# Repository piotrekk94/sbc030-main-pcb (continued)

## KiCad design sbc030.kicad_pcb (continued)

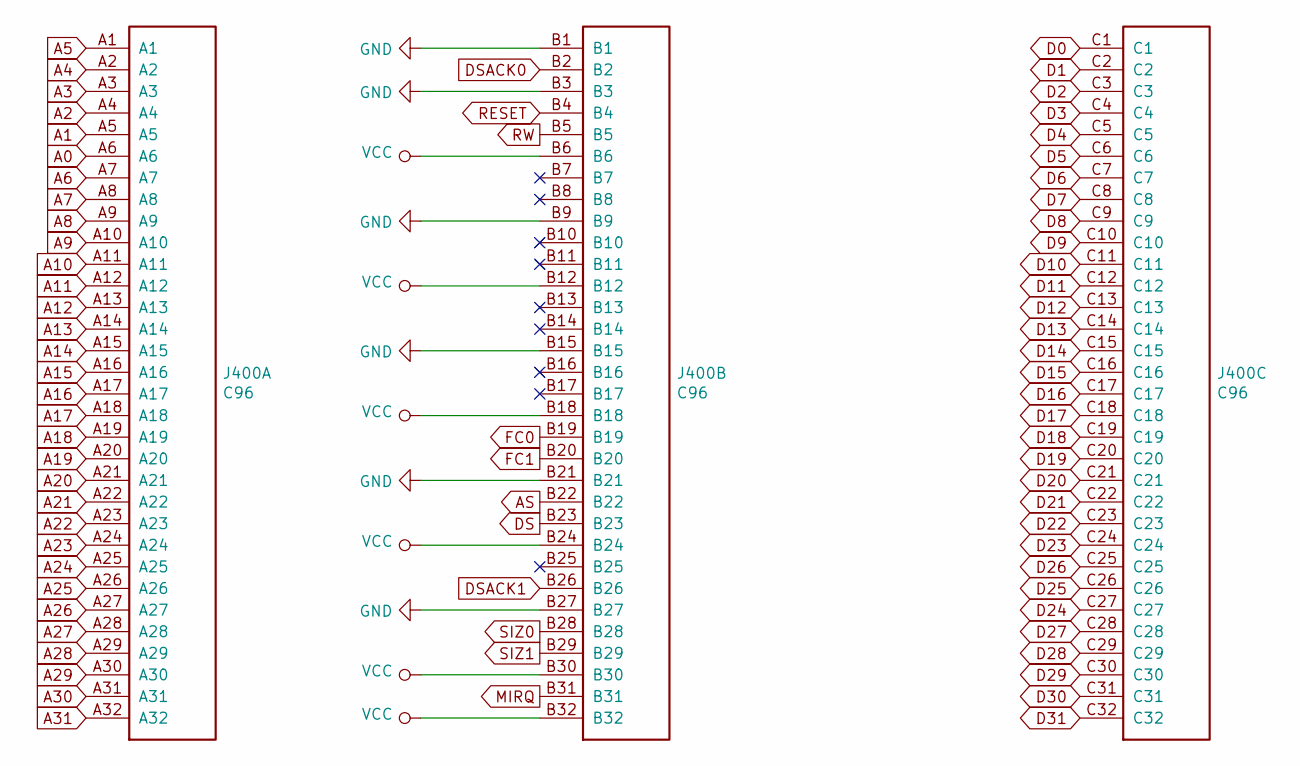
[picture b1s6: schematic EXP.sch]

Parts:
J400: C96; C96ABCM

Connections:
A0: J400.A6; also elsewhere on the board
A1: J400.A5; also elsewhere on the board
A2: J400.A4; also elsewhere on the board
A3: J400.A3; also elsewhere on the board
A4: J400.A2; also elsewhere on the board
A5: J400.A1; also elsewhere on the board
A6: J400.A7; also elsewhere on the board
A7: J400.A8; also elsewhere on the board
A8: J400.A9; also elsewhere on the board
A9: J400.A10; also elsewhere on the board
A10: J400.A11; also elsewhere on the board
A11: J400.A12; also elsewhere on the board
A12: J400.A13; also elsewhere on the board
A13: J400.A14; also elsewhere on the board
A14: J400.A15; also elsewhere on the board
A15: J400.A16; also elsewhere on the board
A16: J400.A17; also elsewhere on the board
A17: J400.A18; also elsewhere on the board
A18: J400.A19; also elsewhere on the board
A19: J400.A20; also elsewhere on the board
A20: J400.A21; also elsewhere on the board
A21: J400.A22; also elsewhere on the board
A22: J400.A23; also elsewhere on the board
A23: J400.A24; also elsewhere on the board
A24: J400.A25; also elsewhere on the board
A25: J400.A26; also elsewhere on the board
A26: J400.A27; also elsewhere on the board
A27: J400.A28; also elsewhere on the board
A28: J400.A29; also elsewhere on the board
A29: J400.A30; also elsewhere on the board
A30: J400.A31; also elsewhere on the board
A31: J400.A32; also elsewhere on the board
AS: J400.B22; also elsewhere on the board
D0: J400.C1; also elsewhere on the board
D1: J400.C2; also elsewhere on the board
D2: J400.C3; also elsewhere on the board
D3: J400.C4; also elsewhere on the board
D4: J400.C5; also elsewhere on the board
D5: J400.C6; also elsewhere on the board
D6: J400.C7; also elsewhere on the board
D7: J400.C8; also elsewhere on the board
D8: J400.C9; also elsewhere on the board
D9: J400.C10; also elsewhere on the board
D10: J400.C11; also elsewhere on the board
D11: J400.C12; also elsewhere on the board
D12: J400.C13; also elsewhere on the board
D13: J400.C14; also elsewhere on the board
D14: J400.C15; also elsewhere on the board
D15: J400.C16; also elsewhere on the board
D16: J400.C17; also elsewhere on the board
D17: J400.C18; also elsewhere on the board
D18: J400.C19; also elsewhere on the board
D19: J400.C20; also elsewhere on the board
D20: J400.C21; also elsewhere on the board
D21: J400.C22; also elsewhere on the board
D22: J400.C23; also elsewhere on the board
D23: J400.C24; also elsewhere on the board
D24: J400.C27; also elsewhere on the board
D25: J400.C26; also elsewhere on the board
D26: J400.C25; also elsewhere on the board
D27: J400.C28; also elsewhere on the board
D28: J400.C29; also elsewhere on the board
D29: J400.C30; also elsewhere on the board
D30: J400.C31; also elsewhere on the board
D31: J400.C32; also elsewhere on the board
DS: J400.B23; also elsewhere on the board
DSACK0: J400.B2; also elsewhere on the board
DSACK1: J400.B26; also elsewhere on the board
FC0: J400.B19; also elsewhere on the board
FC1: J400.B20; also elsewhere on the board
GND: J400.B1, J400.B3, J400.B9, J400.B15, J400.B21, J400.B27; also elsewhere on the board
MIRQ: J400.B31; also elsewhere on the board
RESET: J400.B4; also elsewhere on the board
RW: J400.B5; also elsewhere on the board
SIZ0: J400.B28; also elsewhere on the board
SIZ1: J400.B29; also elsewhere on the board
VCC: J400.B6, J400.B12, J400.B18, J400.B24, J400.B30, J400.B32; also elsewhere on the board

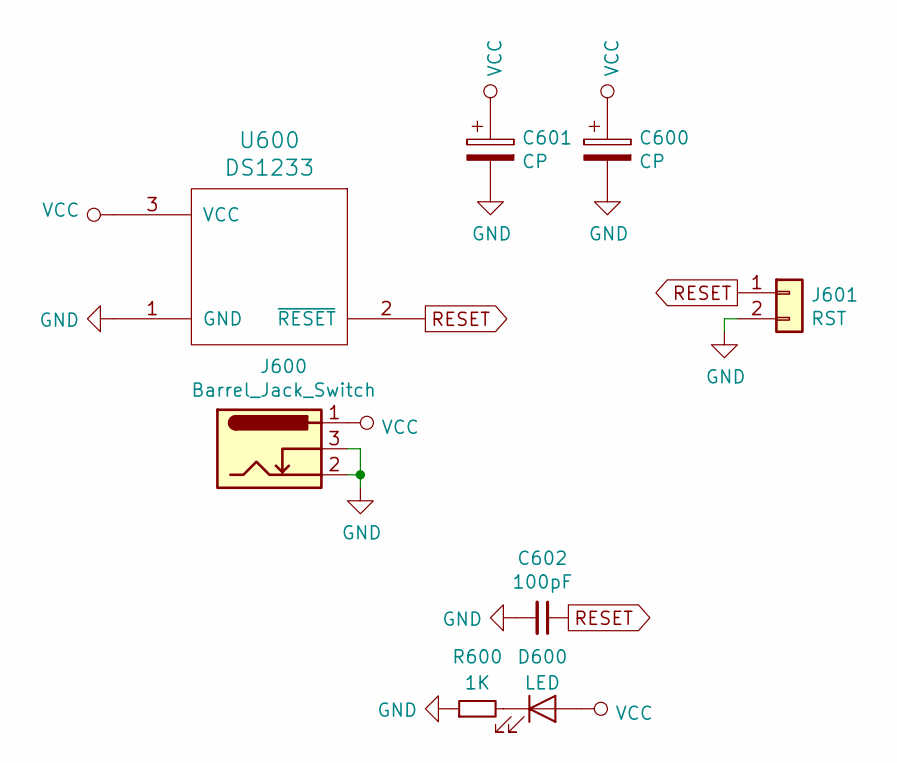
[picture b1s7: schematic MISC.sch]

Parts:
C600, C601: CP; CP_Elec_5x5.4
C602: 100pF; C_0603_1608Metric_Pad1.05x0.95mm_HandSolder
D600: LED; D_0603_1608Metric_Pad1.05x0.95mm_HandSolder
J600: Barrel_Jack_Switch; BarrelJack_Horizontal
J601: RST; PinHeader_1x02_P2.54mm_Vertical
R600: 1K; R_0603_1608Metric_Pad1.05x0.95mm_HandSolder
U600: DS1233; TO-92_Inline

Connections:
GND: C600.2, C601.2, C602.2, J600.2, J600.3, J601.2, R600.1, U600.1 (GND); also elsewhere on the board
unnamed: D600.1 (K), R600.2
RESET: C602.1, J601.1, U600.2 (~RESET); also elsewhere on the board
VCC: C600.1, C601.1, D600.2 (A), J600.1, U600.3 (VCC); also elsewhere on the board

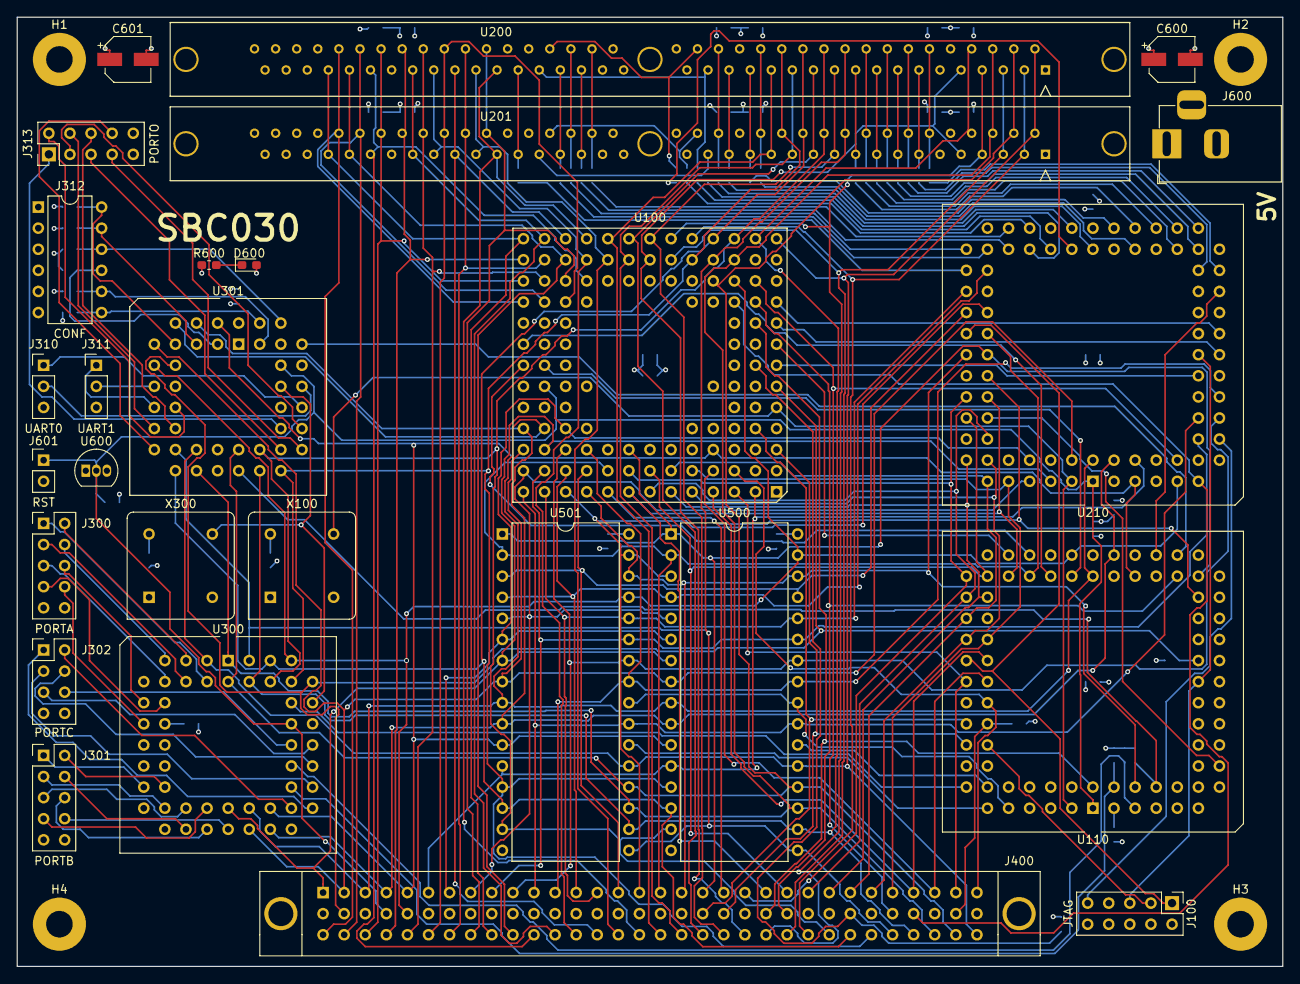
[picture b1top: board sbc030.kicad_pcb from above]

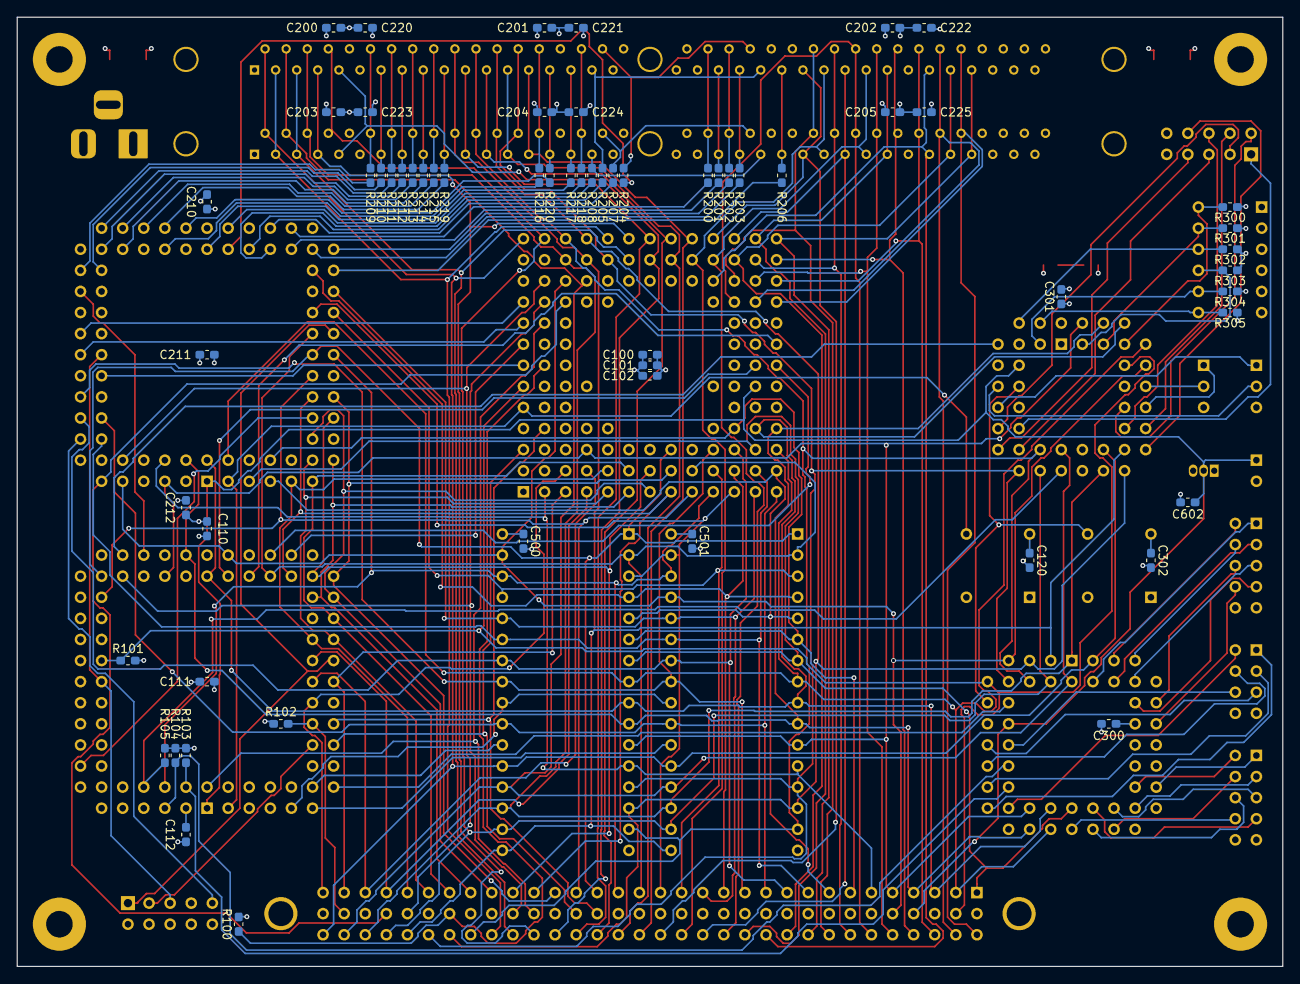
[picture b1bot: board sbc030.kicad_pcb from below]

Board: 4 copper layers, 152.4 x 114.3 mm, 92 parts (61 on the bottom side), 183 nets.

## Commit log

2019-01-19 add relative paths to libraries
